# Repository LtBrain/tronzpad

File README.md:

# **Tronzpad**
Tronzpad is a 12 key + 1 encoder macropad that has 12 individually addressable LEDs to provide underglow & backlighting.
It was developed for an entry for **Hackclub Highway**'s YSWS project (Hackpad) and has the ability to perform **macros** and other
cool stuff with VIAL & QMK.

## Features
   - [x] **12 Cherry MX switches**  
   - [x] **EC-11 Rotary Encoder + Push Button**  
   - [x] **12 Individually Adressable SK6812 MINI LEDs**  
   - [x] **Custom QMK and VIAL Features**  
   - [x] **Powered By A XIAO RP2040**

## PCB

All of the circuitry and PCB design was done with KiCAD 8.0 on Windows 11

#### Schematic

#### PCB Design

Credits to Joe Scotto for the footprints.

## Firmware

QMK and VIAL are meant to be used on Tronzpad for firmware.
   - [x] **Customizable keymap and layout**
   - [x] **12 keys for macros**
   - [x] **Compilable with QMK MSYS on Win11 and Linux (MacOS not tested)**
   - [x] **Real-time/On the fly configuration**
   - [x] **Layer Switching**  
### **How to Compile the Firmware**  
```qmk compile -kb tronzpad -km default```  
  
Paste this into a **MSYS** terminal on Windows or into a Linux terminal with **QMK** already setup.  
(You have to be in the **directory** for this to work)

## Case Assembly
   The case for the Tronzpad was designed to be minimalistic, exposing the graphics on the PCB silkscreen. It is composed of two 3D printed parts, a plate piece and the main assembly.
   The case has 4 2.9mm holes designed to accommodate M3 screws to hold the PCB in place. The plate sits on top of the PCB's top layer to provide a cosmetic/semi-functional layer for 
   the switches to be seated in. 

   ### Plate

   ### Main Case

## Bill of Materials  

| Quantity | Component | Description |
| --- | --- | --- |
| `1` | **Seeed Studio XIAO RP2040** | MCU |
| `12` | **Cherry MX Keyswitches** | I/O |
| `1` | **EC11 Rotary Encoder** | I/O |
| `13` | **1N4148 Diodes** | Support |
| `15` | **SK6812 MINI LEDs** | I/O | 
| `12` | **DSA Keycaps** | Support |
| `4` | **M3x16mm Screws**| Support |
| `1` | **Case Plate**| Support |
| `1` | **Main Case**| Support |
| `1` | **PCB (From JLCPCB)**| Circuit |  

**Summer, 2025**

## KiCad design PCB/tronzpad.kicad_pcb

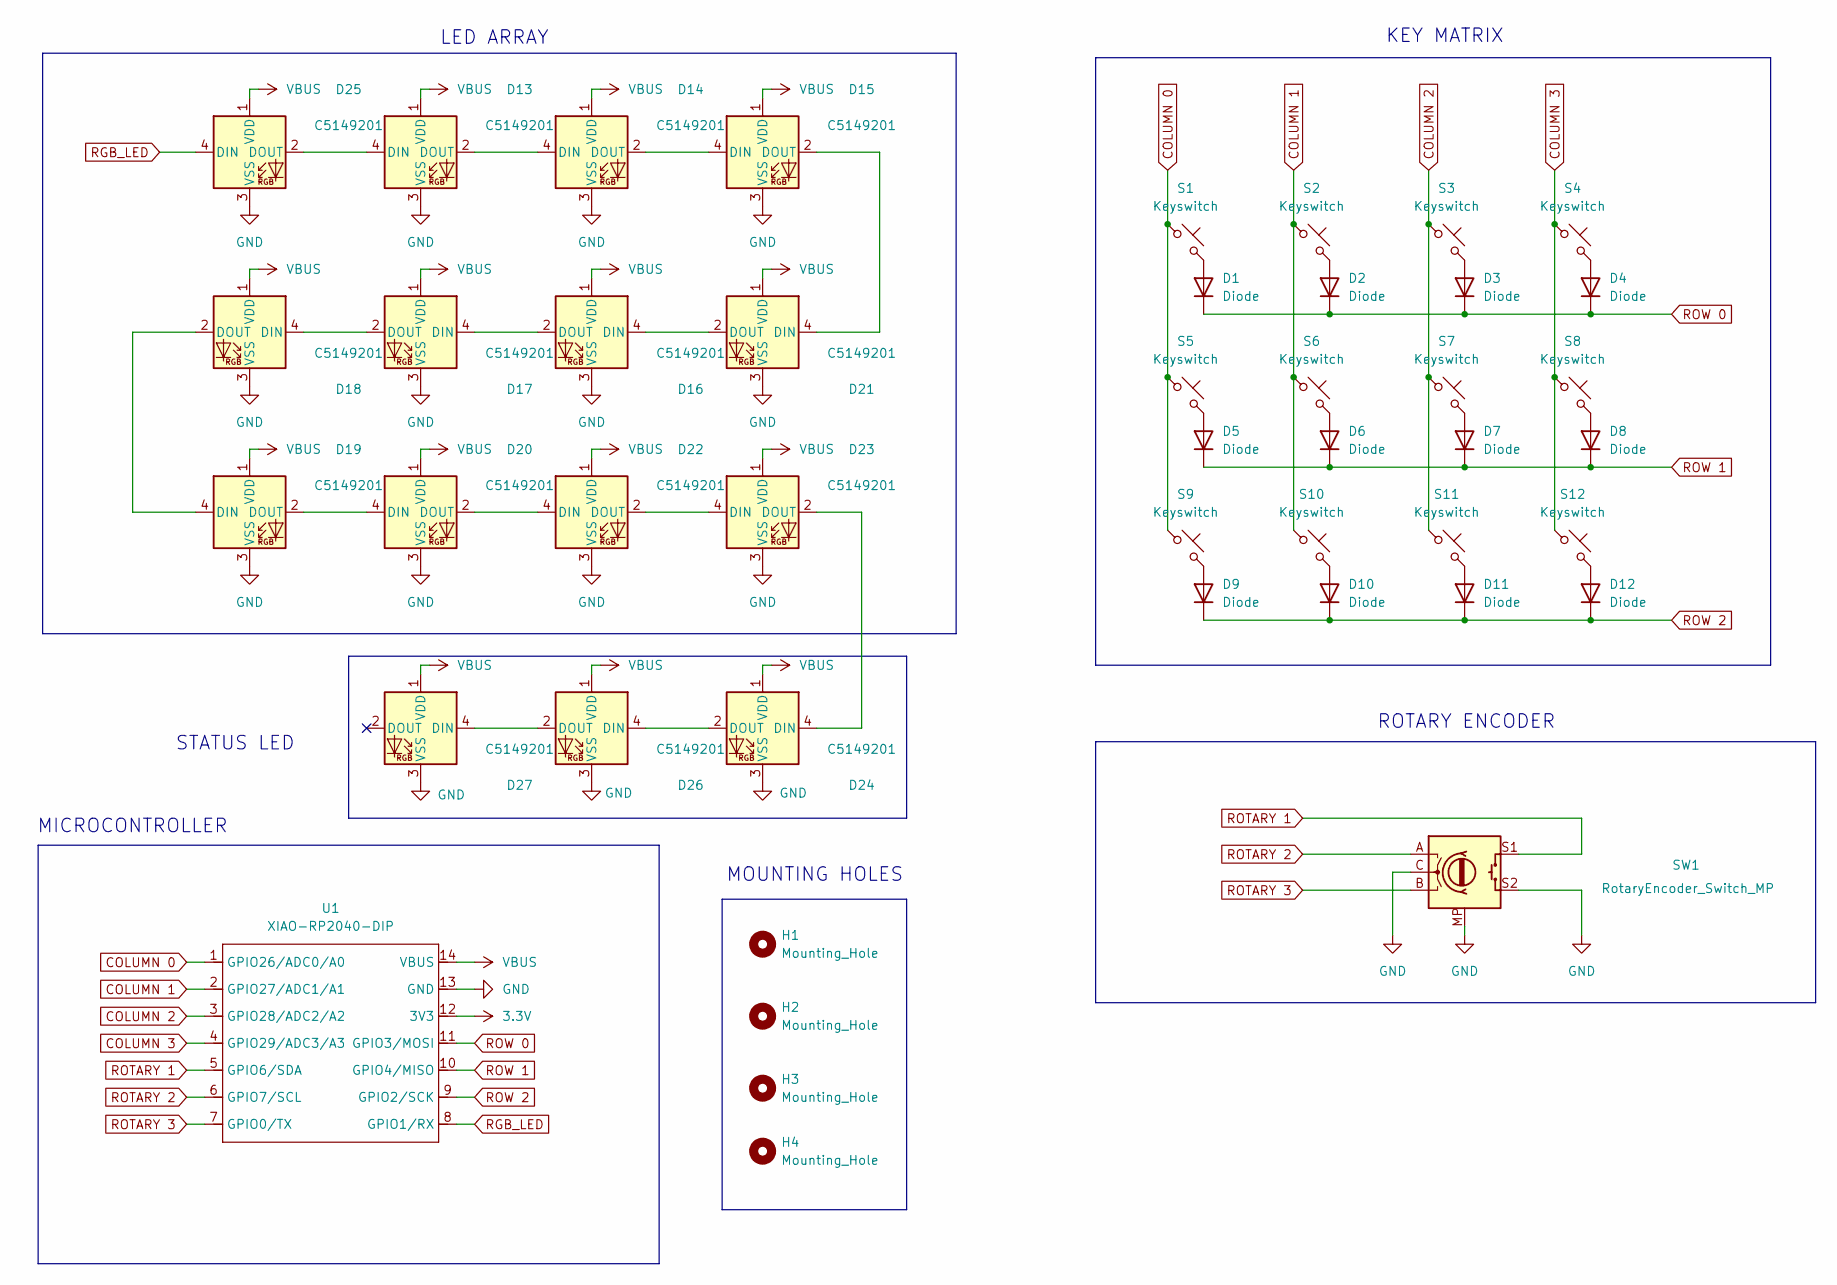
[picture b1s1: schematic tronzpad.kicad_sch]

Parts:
D1, D2, D3, D4, D5, D6, D7, D8, D9, D10, D11, D12: Diode; D_DO-35_SOD27_P7.62mm_Horizontal
D13, D14, D15, D16, D17, D18, D19, D20, D21, D22, D23, D24, D25, D26, D27: LED_SK6812MINI; LCSC C5149201
H1, H2, H3, H4: Mounting_Hole; MountingHole_3.2mm_M3_DIN965
S1, S2, S3, S4, S5, S6, S7, S8, S9, S10, S11, S12: Keyswitch; SW_Cherry_MX_1.00u_PCB
SW1: RotaryEncoder_Switch_MP; RotaryEncoder_Alps_EC11E-Switch_Vertical_H20mm
U1: XIAO-RP2040-DIP

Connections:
3.3V: U1.12 (3V3)
COLUMN 1: S1.2, S5.2, S9.2, U1.1 (GPIO26/ADC0/A0)
COLUMN 2: S2.2, S6.2, S10.2, U1.2 (GPIO27/ADC1/A1)
COLUMN 3: S3.2, S7.2, S11.2, U1.3 (GPIO28/ADC2/A2)
COLUMN 4: S4.2, S8.2, S12.2, U1.4 (GPIO29/ADC3/A3)
GND: D13.3 (VSS), D14.3 (VSS), D15.3 (VSS), D16.3 (VSS), D17.3 (VSS), D18.3 (VSS), D19.3 (VSS), D20.3 (VSS), D21.3 (VSS), D22.3 (VSS), D23.3 (VSS), D24.3 (VSS), D25.3 (VSS), D26.3 (VSS), D27.3 (VSS), SW1.C, SW1.MP, SW1.S2, U1.13 (GND)
unnamed: D1.2 (A), S1.1
unnamed: D2.2 (A), S2.1
unnamed: D3.2 (A), S3.1
unnamed: D4.2 (A), S4.1
unnamed: D5.2 (A), S5.1
unnamed: D6.2 (A), S6.1
unnamed: D7.2 (A), S7.1
unnamed: D8.2 (A), S8.1
unnamed: D9.2 (A), S9.1
unnamed: D10.2 (A), S10.1
unnamed: D11.2 (A), S11.1
unnamed: D12.2 (A), S12.1
unnamed: D13.4 (DIN), D25.2 (DOUT)
unnamed: D13.2 (DOUT), D14.4 (DIN)
unnamed: D14.2 (DOUT), D15.4 (DIN)
unnamed: D15.2 (DOUT), D21.4 (DIN)
unnamed: D16.4 (DIN), D21.2 (DOUT)
unnamed: D16.2 (DOUT), D17.4 (DIN)
unnamed: D17.2 (DOUT), D18.4 (DIN)
unnamed: D18.2 (DOUT), D19.4 (DIN)
unnamed: D19.2 (DOUT), D20.4 (DIN)
unnamed: D20.2 (DOUT), D22.4 (DIN)
unnamed: D22.2 (DOUT), D23.4 (DIN)
unnamed: D23.2 (DOUT), D24.4 (DIN)
unnamed: D24.2 (DOUT), D26.4 (DIN)
unnamed: D26.2 (DOUT), D27.4 (DIN)
RGB_LED: D25.4 (DIN), U1.8 (GPIO1/RX)
ROTARY 1: SW1.S1, U1.5 (GPIO6/SDA)
ROTARY 2: SW1.A, U1.6 (GPIO7/SCL)
ROTARY 3: SW1.B, U1.7 (GPIO0/TX)
ROW 1: D1.1 (K), D2.1 (K), D3.1 (K), D4.1 (K), U1.11 (GPIO3/MOSI)
ROW 2: D5.1 (K), D6.1 (K), D7.1 (K), D8.1 (K), U1.10 (GPIO4/MISO)
ROW 3: D9.1 (K), D10.1 (K), D11.1 (K), D12.1 (K), U1.9 (GPIO2/SCK)
VBUS: D13.1 (VDD), D14.1 (VDD), D15.1 (VDD), D16.1 (VDD), D17.1 (VDD), D18.1 (VDD), D19.1 (VDD), D20.1 (VDD), D21.1 (VDD), D22.1 (VDD), D23.1 (VDD), D24.1 (VDD), D25.1 (VDD), D26.1 (VDD), D27.1 (VDD), U1.14 (VBUS)

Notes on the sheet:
ROTARY ENCODER
LED ARRAY
MOUNTING HOLES
MICROCONTROLLER
STATUS LED
KEY MATRIX

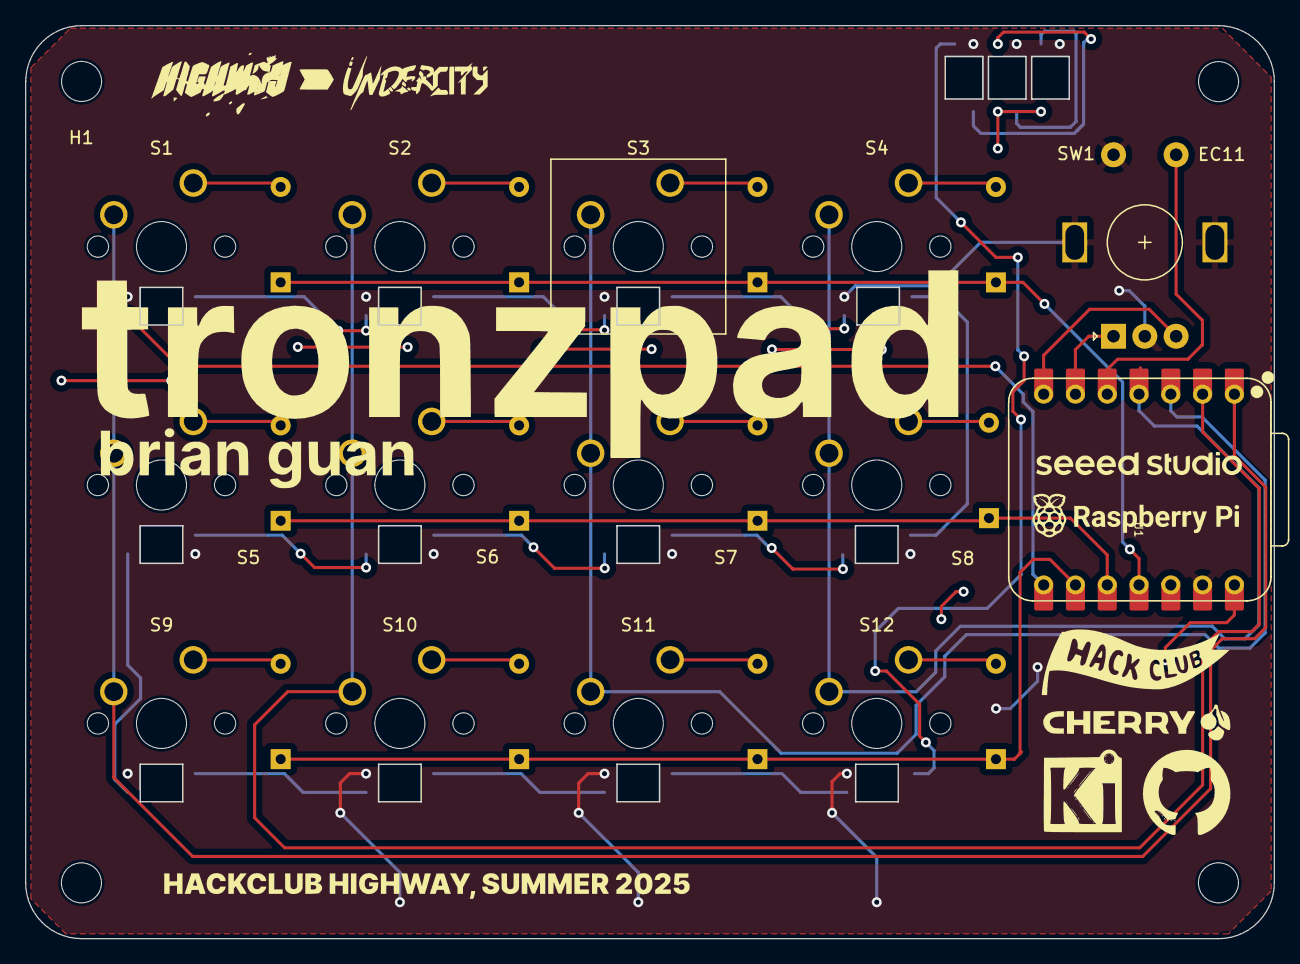
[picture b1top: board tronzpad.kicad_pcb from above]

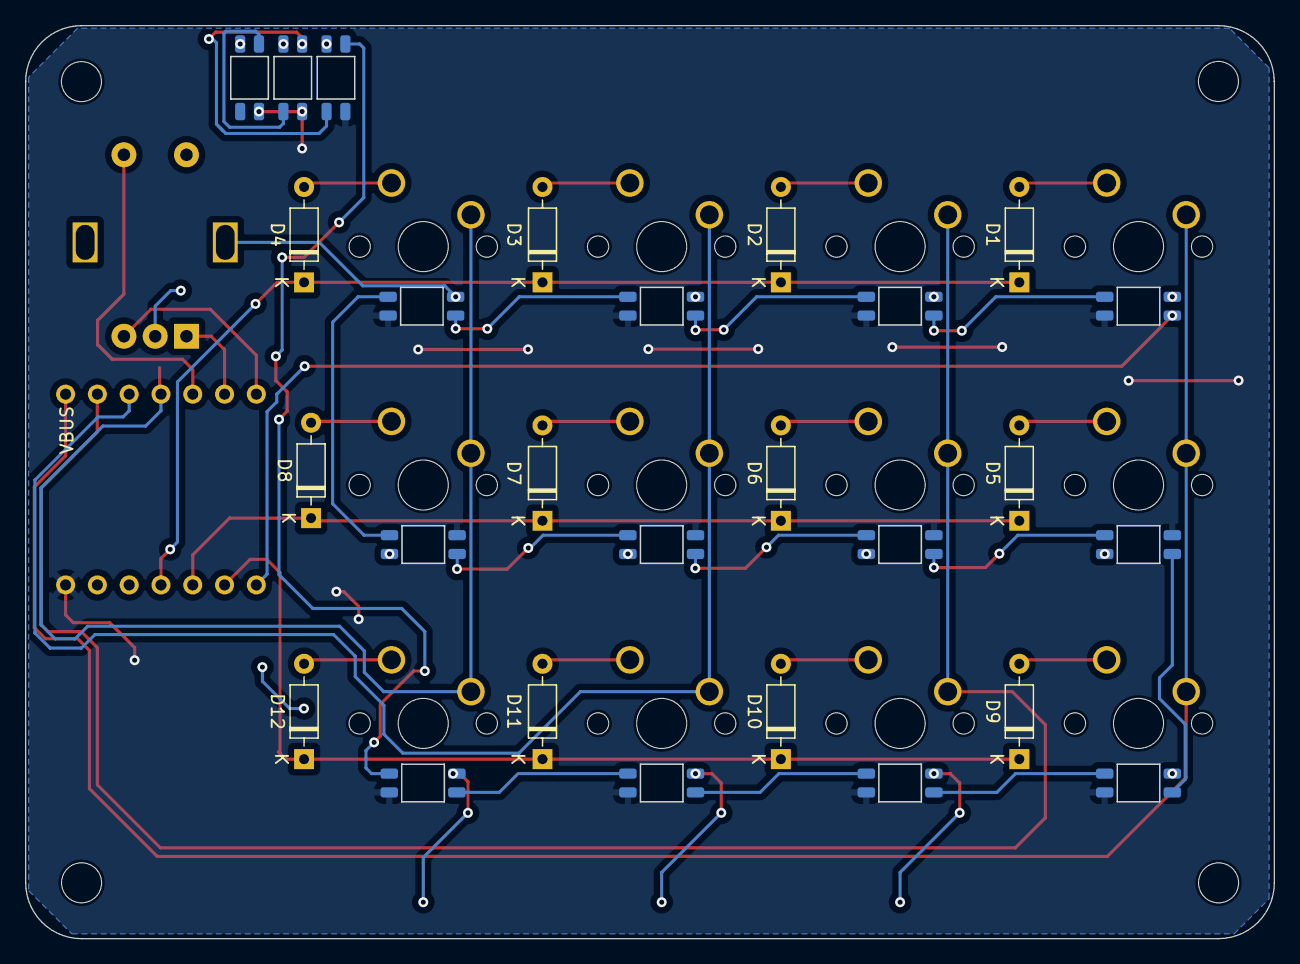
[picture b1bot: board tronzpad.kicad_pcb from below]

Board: 2 copper layers, 99.8 x 72.9 mm, 45 parts (27 on the bottom side), 39 nets.

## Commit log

2025-07-02 add folders & commit kicad files
2025-07-02 add schematic pdf rev1
2025-07-02 actually put the right pdf in
2025-07-03 add gerbers
2025-07-03 add gerber.zip
2025-07-05 more pcb and schematic changes
2025-07-05 qmk firmware (uncompiled)
2025-07-06 add CAD model for entire hackpad
2025-07-06 remove unneccessary pcb files and add pcb pdf
2025-07-06 get rid of more unnecessary files
2025-07-07 add loads of stuff to production
2025-07-08 overload the readme
2025-07-09 encoder and VID/PID addition to firmware
2025-07-11 add full rgb matrix, commit before VIAL port
2025-07-11 vial flavored firmware
